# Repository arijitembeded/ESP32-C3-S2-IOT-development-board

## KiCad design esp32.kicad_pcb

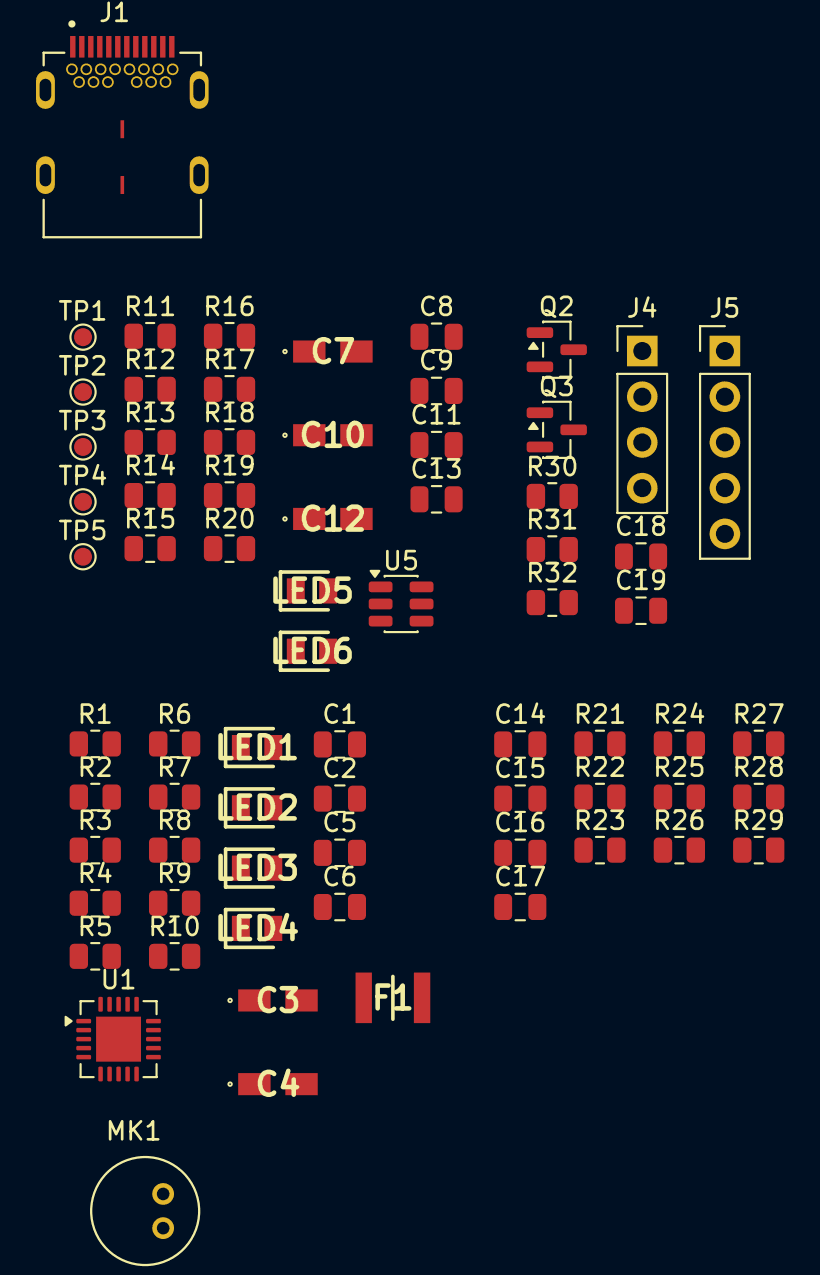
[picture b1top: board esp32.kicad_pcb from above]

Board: 4 copper layers, 71 parts (0 on the bottom side), 40 nets, no tracks yet.

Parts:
C1, C2, C5, C9, C11, C13, C14, C15, C16, C17, C18: 0.1u; C_0805_2012Metric
C3, C4, C10, C12: 10u; T491A
C6: 1 u; C_0805_2012Metric
C7: 4.7uF; T491A
C8: 0.1uF; C_0805_2012Metric
C19: 1u; C_0805_2012Metric
F1: 0ZCH0110AF2E; FUSC3226X100N
J1: SS-52400-002; BELFUSE_SS-52400-002
J4: Conn_01x04_Pin; PinHeader_1x04_P2.54mm_Vertical
J5: Conn_01x05_Pin; PinHeader_1x05_P2.54mm_Vertical
LED1, LED4, LED6: LTST-C170KRKT; LEDC2012X120N
LED2, LED5: LTST-C170GKT; LEDC2012X120N
LED3: LTST-C170TBKT; LEDC2012X120N
MK1: CMC-5042PF-AC; CUI_CMC-5042PF-AC
Q2, Q3: BC817; SOT-23
R1, R2: 10 K; R_0805_2012Metric
R3, R4: 5k1; R_0805_2012Metric
R5: 20K; R_0805_2012Metric
R6: 2k; R_0805_2012Metric
R7, R8, R9, R10, R14, R18: 470; R_0805_2012Metric
R11, R13: 22.1K; R_0805_2012Metric
R12: 47.5K; R_0805_2012Metric
R15, R16, R17, R20: 50; R_0805_2012Metric
R19, R23, R25, R30, R31, R32: 10K; R_0805_2012Metric
R21, R22: 4K7; R_0805_2012Metric
R24: 100K; R_0805_2012Metric
R26, R27: 1M; R_0805_2012Metric
R28, R29: 2K; R_0805_2012Metric
TP1: Test MOSI; TestPoint_Pad_D1.0mm
TP2: TEST MISO; TestPoint_Pad_D1.0mm
TP3: TEST SCLK; TestPoint_Pad_D1.0mm
TP4: TEST CD_SD; TestPoint_Pad_D1.0mm
TP5: TEST CS; TestPoint_Pad_D1.0mm
U1: MCP73871; QFN-20-1EP_4x4mm_P0.5mm_EP2.5x2.5mm
U5: USBLC6-2SC6; SOT-23-6

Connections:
+3.3V: C4.1, C5.1, C7.2, C8.2, C9.1, C10.1, C11.1, C12.1, C13.1, C14.1, C15.1, J4.4, J5.5, LED4.2 (A), LED5.2 (A), LED6.2 (A), R13.1, R19.2, R21.1, R22.1, R23.1, R26.1, R28.1, R32.1
+5V: C2.1, C3.1, U1.1 (OUT), U1.20 (OUT)
/+5V_USB: C6.1, F1.2, LED1.2 (A), LED2.2 (A), LED3.2 (A), U1.2 (VPCC), U1.4 (PROG2), U1.17 (CE), U1.18 (IN), U1.19 (IN)
/CHARGED: R8.2, U1.8 (STAT1/~LBO)
/CHARGING: R9.2, U1.6 (~PG)
/CHARGING_POWER_GOOD: R7.2, U1.7 (STAT2)
/ESP 32-C3-02/BOOT: C18.1, Q3.2 (E)
/ESP 32-C3-02/CD_SD: R19.1, TP4.1
/ESP 32-C3-02/DTS: Q2.2 (E), R31.1
/ESP 32-C3-02/EN: C19.1, Q2.3 (C), R32.2
/ESP 32-C3-02/MIC_OUT: C16.2, R24.2
/ESP 32-C3-02/MISO_DO: R17.2, R20.1, TP2.1
/ESP 32-C3-02/MOSI_DI: R16.2, TP1.1
/ESP 32-C3-02/RTS: Q3.3 (C), R30.1
/ESP 32-C3-02/SCL: J4.2, R22.2
/ESP 32-C3-02/SCLK: R15.1, TP3.1
/ESP 32-C3-02/SDA: J4.3, R21.2
/PWD_LED: LED4.1 (K), R10.1
/USB_DN: J1.A7 (DN1), J1.B7 (DN2), U5.6 (I/O1)
/USB_DP: J1.A6 (DP1), J1.B6 (DP2), U5.4 (I/O2)
/VBAT: U1.14 (V_{BAT}), U1.15 (V_{BAT}), U1.16 (V_{BAT_SENSE})
/VBUS: C1.1, F1.1, J1.A4 (VBUSA1), J1.A9 (VBUSA2), J1.B4 (VBUSB1), J1.B9 (VBUSB2), R11.1, U5.5 (VBUS)
GND: C1.2, C2.2, C3.2, C4.2, C5.2, C6.2, C7.1, C8.1, C9.2, C10.2, C11.2, C12.2, C13.2, C14.2, C15.2, C16.1, C17.1, C18.2, C19.2, J1.A1 (GNDA1), J1.A12 (GNDA2), J1.B1 (GNDB1), J1.B12 (GNDB2), J1.G1 (GND/SHIELD), J1.G2 (GND/SHIELD), J1.G3 (GND/SHIELD), J1.G4 (GND/SHIELD), J1.S1 (GND/SHIELD), J1.S2 (GND/SHIELD), J1.S3 (GND/SHIELD), J1.S4 (GND/SHIELD), J4.1, J5.1, MK1.GND, R1.2, R2.2, R3.1, R4.1, R5.1, R6.1, R10.2, R12.2, R24.1, R25.1, R25.2, R27.2, U1.3 (SEL), U1.10 (V_{SS}), U1.11 (V_{SS}), U1.21 (V_{SS}), U5.2 (GND)
unnamed: C17.2, R28.2, R29.1
unnamed: J1.A5 (CC1), R4.2
unnamed: J1.B5 (CC2), R3.2
unnamed: LED1.1 (K), R9.1
unnamed: LED2.1 (K), R8.1
unnamed: LED3.1 (K), R7.1
unnamed: LED5.1 (K), R18.1
unnamed: LED6.1 (K), R14.1
unnamed: Q2.1 (B), R30.2
unnamed: Q3.1 (B), R31.2
unnamed: R26.2, R27.1
unnamed: R6.2, U1.13 (PROG1)
unnamed: R5.2, U1.12 (PROG3)
unnamed: R2.1, U1.5 (THERM)
unnamed: R1.1, U1.9 (~TE)
unnamed: R11.2, R12.1
unnamed: MK1.OUT, R29.2

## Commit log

2025-10-20 flash memory schematics added
2025-10-20 test point added to the schematics
2025-10-22 BME 280 temperature and humidity sensor
2025-10-22 extra 3.3v symbol removed
2025-11-07 UI workig
2025-11-26 latest new dev
2025-12-14 next working on that part
